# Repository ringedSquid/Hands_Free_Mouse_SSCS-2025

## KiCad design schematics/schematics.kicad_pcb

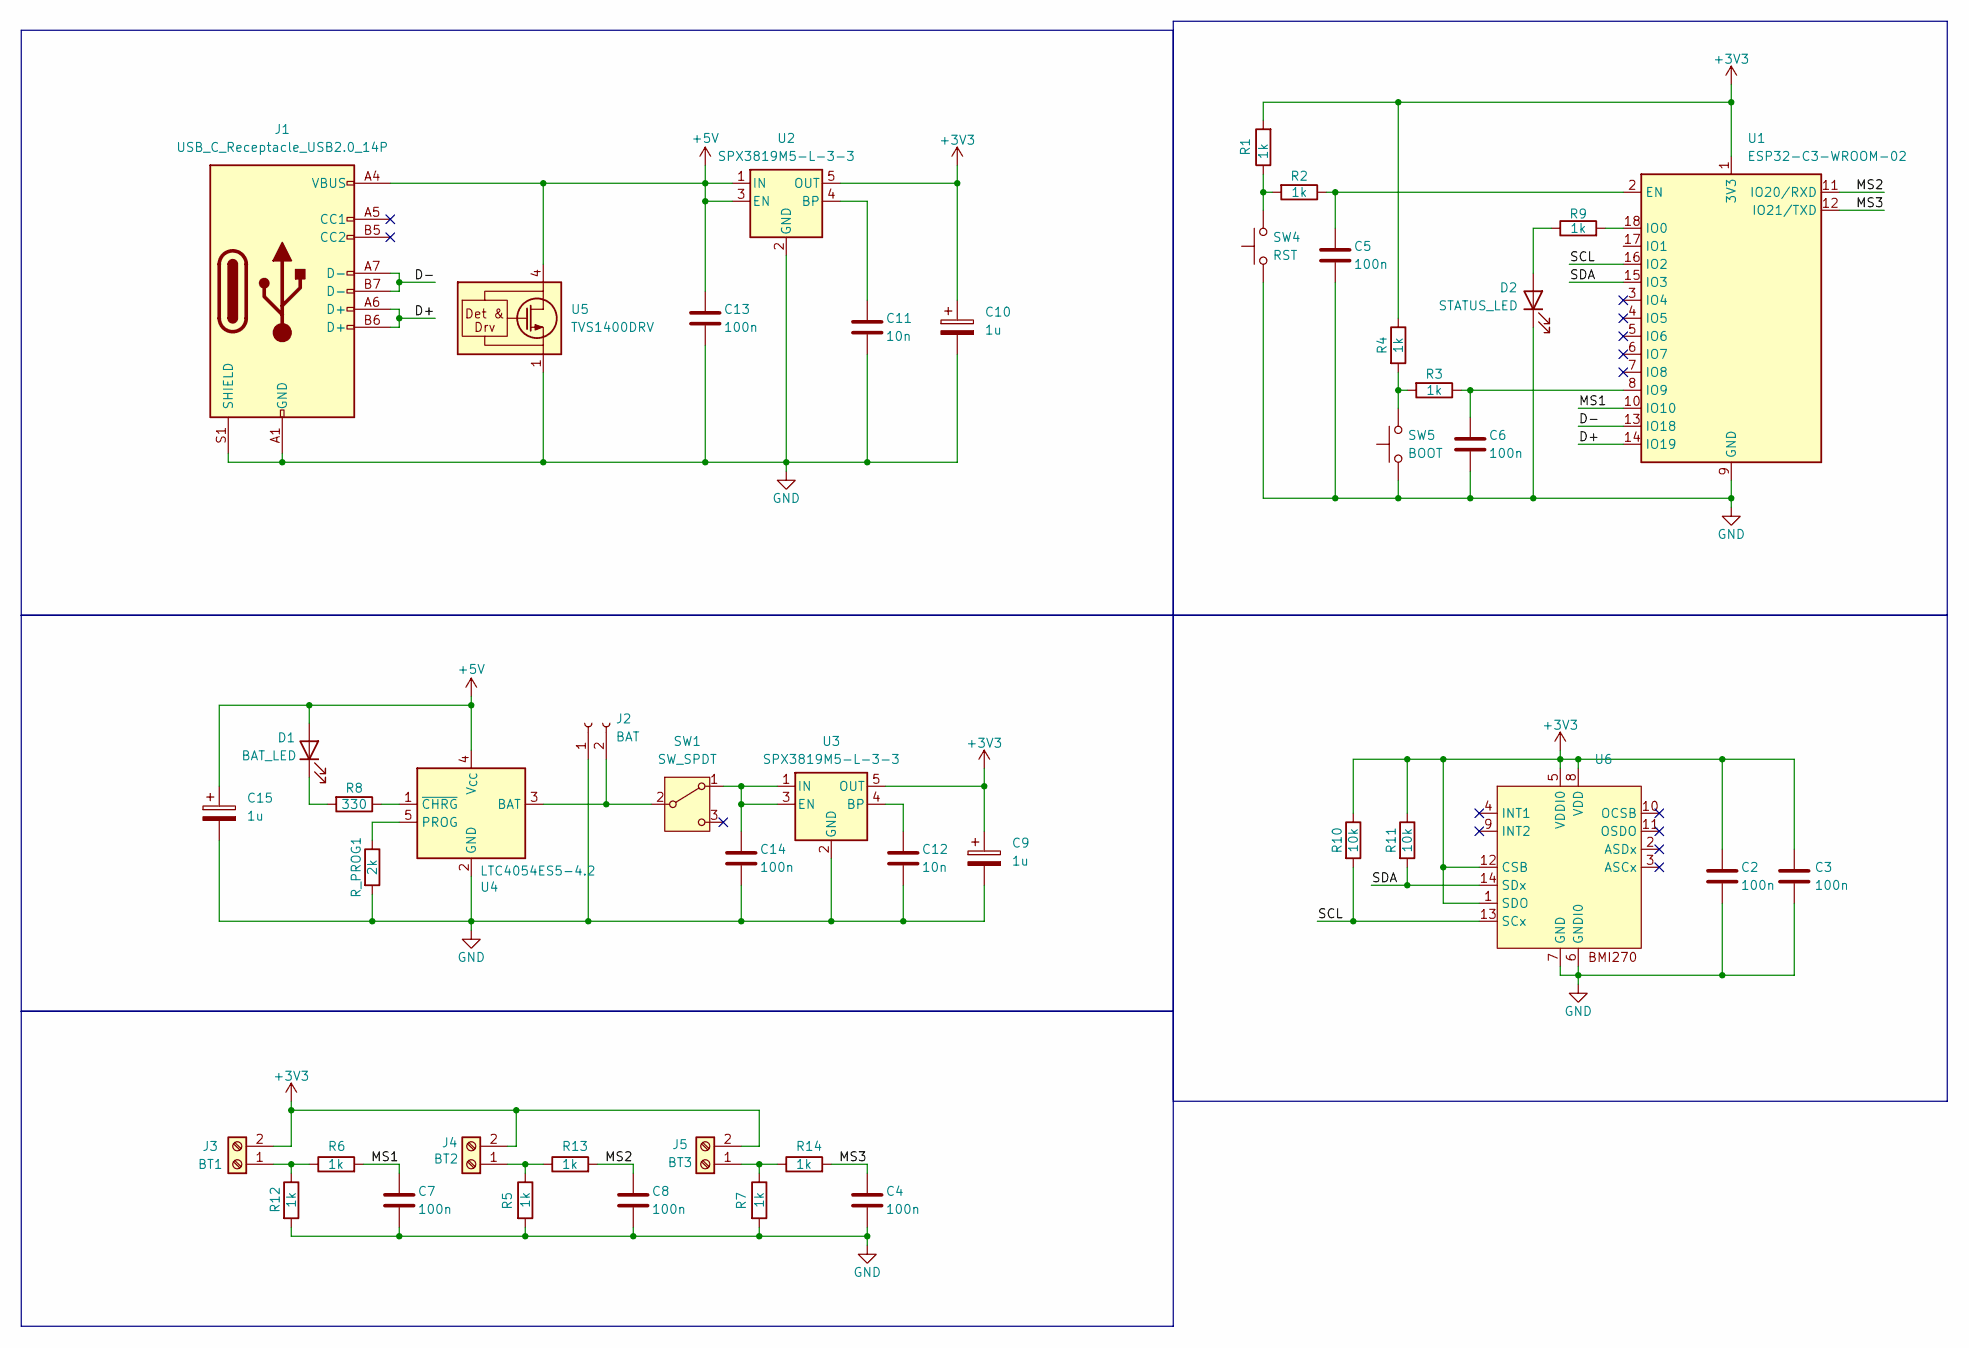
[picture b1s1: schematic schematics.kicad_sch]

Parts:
C2, C3, C4, C5, C6, C7, C8, C13, C14: 100n; C_0603_1608Metric
C9, C10, C15: 1u; C_0805_2012Metric
C11, C12: 10n; C_0603_1608Metric
D1: BAT_LED; LED_D1.8mm_W1.8mm_H2.4mm_Horizontal_O1.27mm_Z1.6mm
D2: STATUS_LED; LED_D1.8mm_W1.8mm_H2.4mm_Horizontal_O1.27mm_Z1.6mm
J1: USB_C_Receptacle_USB2.0_14P; USB_C_Receptacle_GCT_USB4110
J2: BAT; JST_PH_B2B-PH-K_1x02_P2.00mm_Vertical
J3: BT1; TerminalBlock_Phoenix_MPT-0,5-2-2.54_1x02_P2.54mm_Horizontal
J4: BT2; TerminalBlock_Phoenix_MPT-0,5-2-2.54_1x02_P2.54mm_Horizontal
J5: BT3; TerminalBlock_Phoenix_MPT-0,5-2-2.54_1x02_P2.54mm_Horizontal
R1, R2, R3, R4, R5, R6, R7, R9, R12, R13, R14: 1k; R_0603_1608Metric
R8: 330; R_0603_1608Metric
R10, R11: 10k; R_0603_1608Metric
R_PROG1: 2k; R_0603_1608Metric
SW1: SW_SPDT; SW_Slide_SPDT_Angled_CK_OS102011MA1Q
SW4: RST; SW_Push_1P1T_NO_CK_KMR2
SW5: BOOT; SW_Push_1P1T_NO_CK_KMR2
U1: ESP32-C3-WROOM-02
U2, U3: SPX3819M5-L-3-3; SOT-23-5
U4: LTC4054ES5-4.2; TSOT-23-5
U5: TVS1400DRV; WSON-6-1EP_2x2mm_P0.65mm_EP1x1.6mm
U6: Bosch_LGA-14_3x2.5mm_P0.5mm

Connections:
+3V3: C2.1, C3.1, C9.1, C10.1, J3.2, J4.2, J5.2, R1.2, R4.1, R10.1, R11.1, U1.1 (3V3), U2.5 (OUT), U3.5 (OUT), U6.1 (SDO), U6.5 (VDDI0), U6.8 (VDD), U6.12 (CSB)
+5V: C13.1, C15.1, D1.2 (A), J1.A4 (VBUS), J1.A9 (VBUS), J1.B4 (VBUS), J1.B9 (VBUS), U2.1 (IN), U2.3 (EN), U4.4 (V_{CC}), U5.4 (IN), U5.5 (IN), U5.6 (IN)
/D+: J1.A6 (D+), J1.B6 (D+), U1.14 (IO19)
/D-: J1.A7 (D-), J1.B7 (D-), U1.13 (IO18)
/MS1: C7.1, R6.2, U1.10 (IO10)
/MS2: C8.1, R13.2, U1.11 (IO20/RXD)
/MS3: C4.1, R14.2, U1.12 (IO21/TXD)
/SCL: R10.2, U1.16 (IO2), U6.13 (SCx)
/SDA: R11.2, U1.15 (IO3), U6.14 (SDx)
GND: C2.2, C3.2, C4.2, C5.2, C6.2, C7.2, C8.2, C9.2, C10.2, C11.2, C12.2, C13.2, C14.2, C15.2, D2.1 (K), J1.A1 (GND), J1.A12 (GND), J1.B1 (GND), J1.B12 (GND), J1.S1 (SHIELD), J2.1, R5.2, R7.2, R12.2, R_PROG1.2, SW4.1, SW5.1, U1.9 (GND), U1.19 (GND), U2.2 (GND), U3.2 (GND), U4.2 (GND), U5.1 (GND), U5.2 (GND), U5.3 (GND), U5.7 (GND), U6.6 (GNDI0), U6.7 (GND)
unnamed: D1.1 (K), R8.2
unnamed: D2.2 (A), R9.1
unnamed: J2.2, SW1.2 (B), U4.3 (BAT)
unnamed: J3.1, R6.1, R12.1
unnamed: J4.1, R5.1, R13.1
unnamed: J5.1, R7.1, R14.1
unnamed: R1.1, R2.2, SW4.2
unnamed: R3.2, R4.2, SW5.2
unnamed: C14.1, SW1.1 (A), U3.1 (IN), U3.3 (EN)
unnamed: C5.1, R2.1, U1.2 (EN)
unnamed: R9.2, U1.18 (IO0)
unnamed: C6.1, R3.1, U1.8 (IO9)
unnamed: C11.1, U2.4 (BP)
unnamed: C12.1, U3.4 (BP)
unnamed: R_PROG1.1, U4.5 (PROG)
unnamed: R8.1, U4.1 (~CHRG)

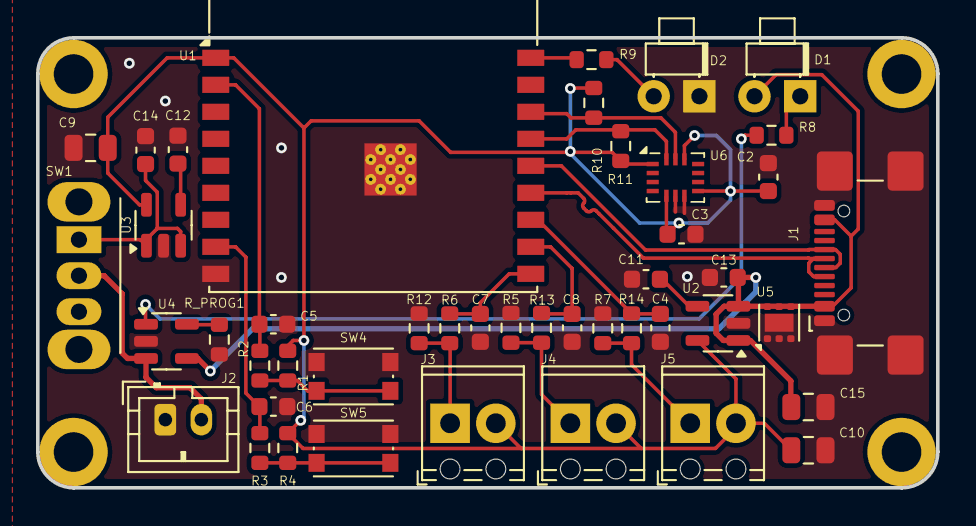
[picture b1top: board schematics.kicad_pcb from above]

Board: 2 copper layers, 50.0 x 25.0 mm, 45 parts (0 on the bottom side), 26 nets.

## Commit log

2025-07-10 added kicad file
2025-07-10 completed schematics, need to start routing to decide I2C and button pinouts
2025-07-15 initial electronics
2025-07-15 completed electronics, ordered parts
2025-07-23 fix i2c pins
2025-07-30 mouse working need to add buttons in hardware and software
2025-07-31 add cad files
